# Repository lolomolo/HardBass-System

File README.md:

# HardBass-System
ESP8266 based meshnet which will monitor only one state; HARDBASS State. 

If the any of the many esp8266 bases sensors detect a HARDBASS-STATE ON all meshnet components will activate.
There are 4 discrete peripheral types. Each is based around the ESP8266_01 Module. 
1; Button|  this platform will only monitor the state of the hardbass button and inform the meshnet of the current state.
2; RasPi|   this platform will inform the raspberry pi when the bardbass state has been switched to on.
3; Relay|   this platform will switch a 10A 120VAC relay when it detects that the hardbass state has been switched on.
4; RGB|     this platform will drive an LED strip to a specific color cycle when it detects that the hardbass state has been switched on.

On detect; the RasPi will procede to raise volume to max and play Tri_Poloski.mp4 on its audio output.
On detect; all illuminating lights in the garage will be switched off by the Relay platform(s)
On detect; rgb strip controls will be highjacked by the RGB platform and go into rave mode

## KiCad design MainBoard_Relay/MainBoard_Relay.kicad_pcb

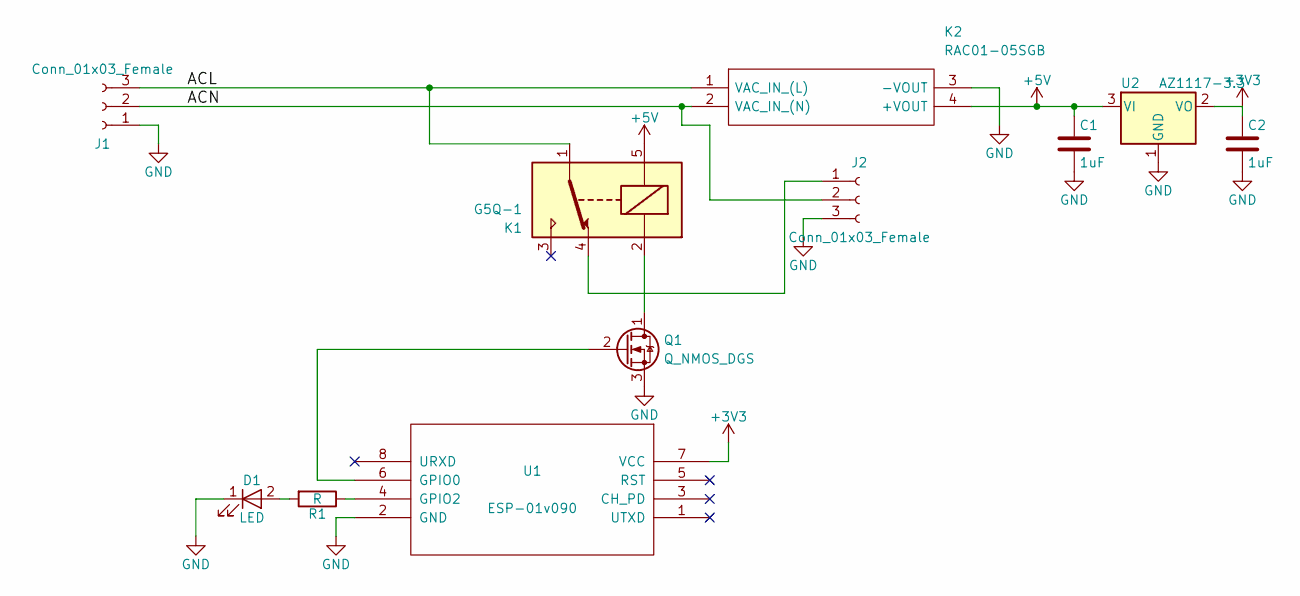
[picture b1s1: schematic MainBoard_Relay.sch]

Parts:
C1, C2: 1uF; C_0805_HandSoldering
D1: LED; LED_0805_HandSoldering
J1, J2: Conn_01x03_Female; PhoenixContact_MCV-G_03x5.08mm_Vertical
K1: G5Q-1; Relay_SPDT_OMRON-G5LE-1
K2: RAC01-05SGB; RAC01_GB; Manufacturer_Part_Number RAC01-05SGB
Q1: Q_NMOS_DGS; SOT-23
R1: R; R_0805_HandSoldering
U1: ESP-01v090; ESP-01
U2: AZ1117-3.3; SOT-223

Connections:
+3V3: C2.1, U1.7 (VCC), U2.2 (VO)
+5V: C1.1, K1.5, K2.4 (+VOUT), U2.3 (VI)
/ACL: J1.3, K1.1, K2.1 (VAC_IN_(L))
/ACN: J1.2, J2.2, K2.2 (VAC_IN_(N))
GND: C1.2, C2.2, D1.1 (K), J1.1, J2.3, K2.3 (-VOUT), Q1.3 (S), U1.2 (GND), U2.1 (GND)
unnamed: D1.2 (A), R1.2
unnamed: J2.1, K1.4
unnamed: K1.2, Q1.1 (D)
unnamed: Q1.2 (G), U1.6 (GPIO0)
unnamed: R1.1, U1.4 (GPIO2)

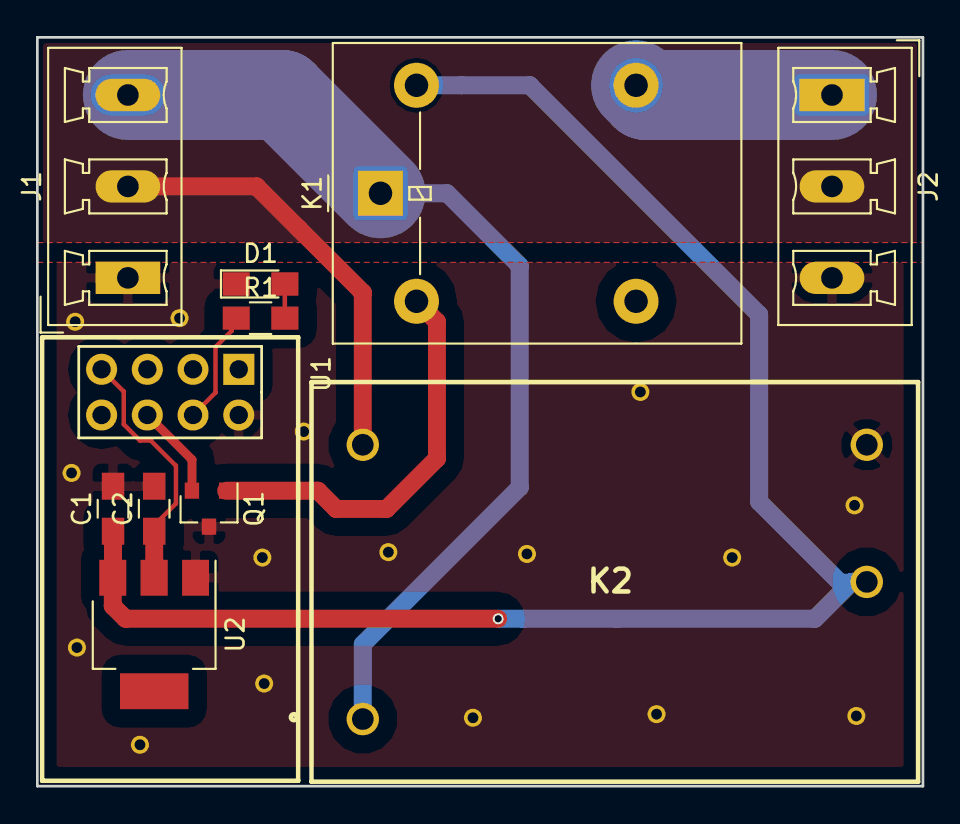
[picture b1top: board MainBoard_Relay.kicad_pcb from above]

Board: 2 copper layers, 49.2 x 41.6 mm, 11 parts (0 on the bottom side), 10 nets.

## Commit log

2018-07-20 RGB and Relay Platform Sch V1
2018-07-20 RGB platform finished
2018-07-21 RGB and Relay platform finished
